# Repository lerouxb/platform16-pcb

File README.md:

# platform 16 PCB

This is the KiCad project for **platform 16** — a compact digital synthesizer built around the Raspberry Pi RP2350 microcontroller. The board hosts 16 potentiometers for real-time parameter control, a high-quality audio output chain, and USB-C for power and an SWD port for development.

## Overview

Platform 16 is a self-contained generative synthesizer platform. The hardware is designed to pair with swappable firmware engines — each one turns the same 16 knobs into a different instrument. A companion [front panel editor](https://github.com/lerouxb/platform16-editor) (web app) generates printable overlays so you can label the knobs for whichever [firmware](https://github.com/lerouxb/plaform16-firmware) is loaded.

## Key Components

| Component | Part | Role |
|---|---|---|
| MCU | **RP2350** (QFN-60) | Dual-core Cortex-M33 — runs synthesis DSP, reads pots, drives I2S audio |
| DAC | **PCM5100A** (TI) | 32-bit stereo I2S DAC — converts digital audio to line-level analog |
| Headphone amp | **PAM8908JER** | Capless stereo headphone amplifier — drives headphones without coupling caps |
| Flash | **W25Q128JVS** (Winbond) | 16 MB QSPI flash for firmware and data storage |
| Analog mux | **CD74HC4067SM** | 16-channel analog multiplexer — reads all 16 pots through a single ADC channel |
| Voltage regulator | **NCP1117-3.3** | 3.3 V LDO powered from USB 5 V |
| Audio jacks | **PJ-320D-A** (×3) | 3.5 mm TRS jacks edge-mounted through board notches |
| Connector | **USB-C 16-pin** | Power and data (with proper CC resistors for USB-C detection) |

## Board Details

- **Dimensions:** ~112 mm × 86 mm with rounded corners
- **Mounting:** 4 × M3 mounting holes in a 69 mm × 46 mm rectangle
- **Audio jacks:** Semicircular edge cutouts allow the 3.5 mm jack barrels to protrude through the top edge
- **Passives:** 0402 throughout for a compact layout
- **Potentiometers:** 16 × 10 kΩ through-hole pots (the namesake of the project)
- **Buttons:** 2 × tactile switches for boot mode and reset

## Architecture

```
USB-C (5V)
  │
  ├─► NCP1117 → 3.3V rail
  │
  ▼
RP2350 ──I2S──► PCM5100A (DAC) ──► PAM8908 (amp) ──► 3.5mm jacks
  │
  ├─► CD74HC4067 mux ◄── 16 pots
  ├─► QSPI flash (W25Q128)
  ├─► 2 buttons
  └─► Clock in/out
```

## Schematic

## PCB Layout

## 3D Render

## Related Projects

- **[Firmware](https://github.com/lerouxb/plaform16-firmware)** — C++ (Pico SDK) running on the RP2350. Three swappable generative synth engines:
  - **SDS** — Stochastic Decay Subtractive (PolyBLEP saw + Moog ladder filter, random sequencer)
  - **PMD** — Phase Modulation with Decay (2-operator FM triads, dual LFOs)
  - **TEP** — Two-tone Euclidean Polymeters (dual detunable saws, 3 independent Euclidean rhythms)
- **[Front Panel Editor](https://github.com/lerouxb/platform16-editor)** — React/TypeScript web app for designing printable panel overlays with labelled knobs matching each firmware's control layout

## Tools

- **KiCad 9.0** — schematic and PCB design
- **Fabrication Toolkit** — JLC-compatible production output (BOM, positions, netlist in `production/`)

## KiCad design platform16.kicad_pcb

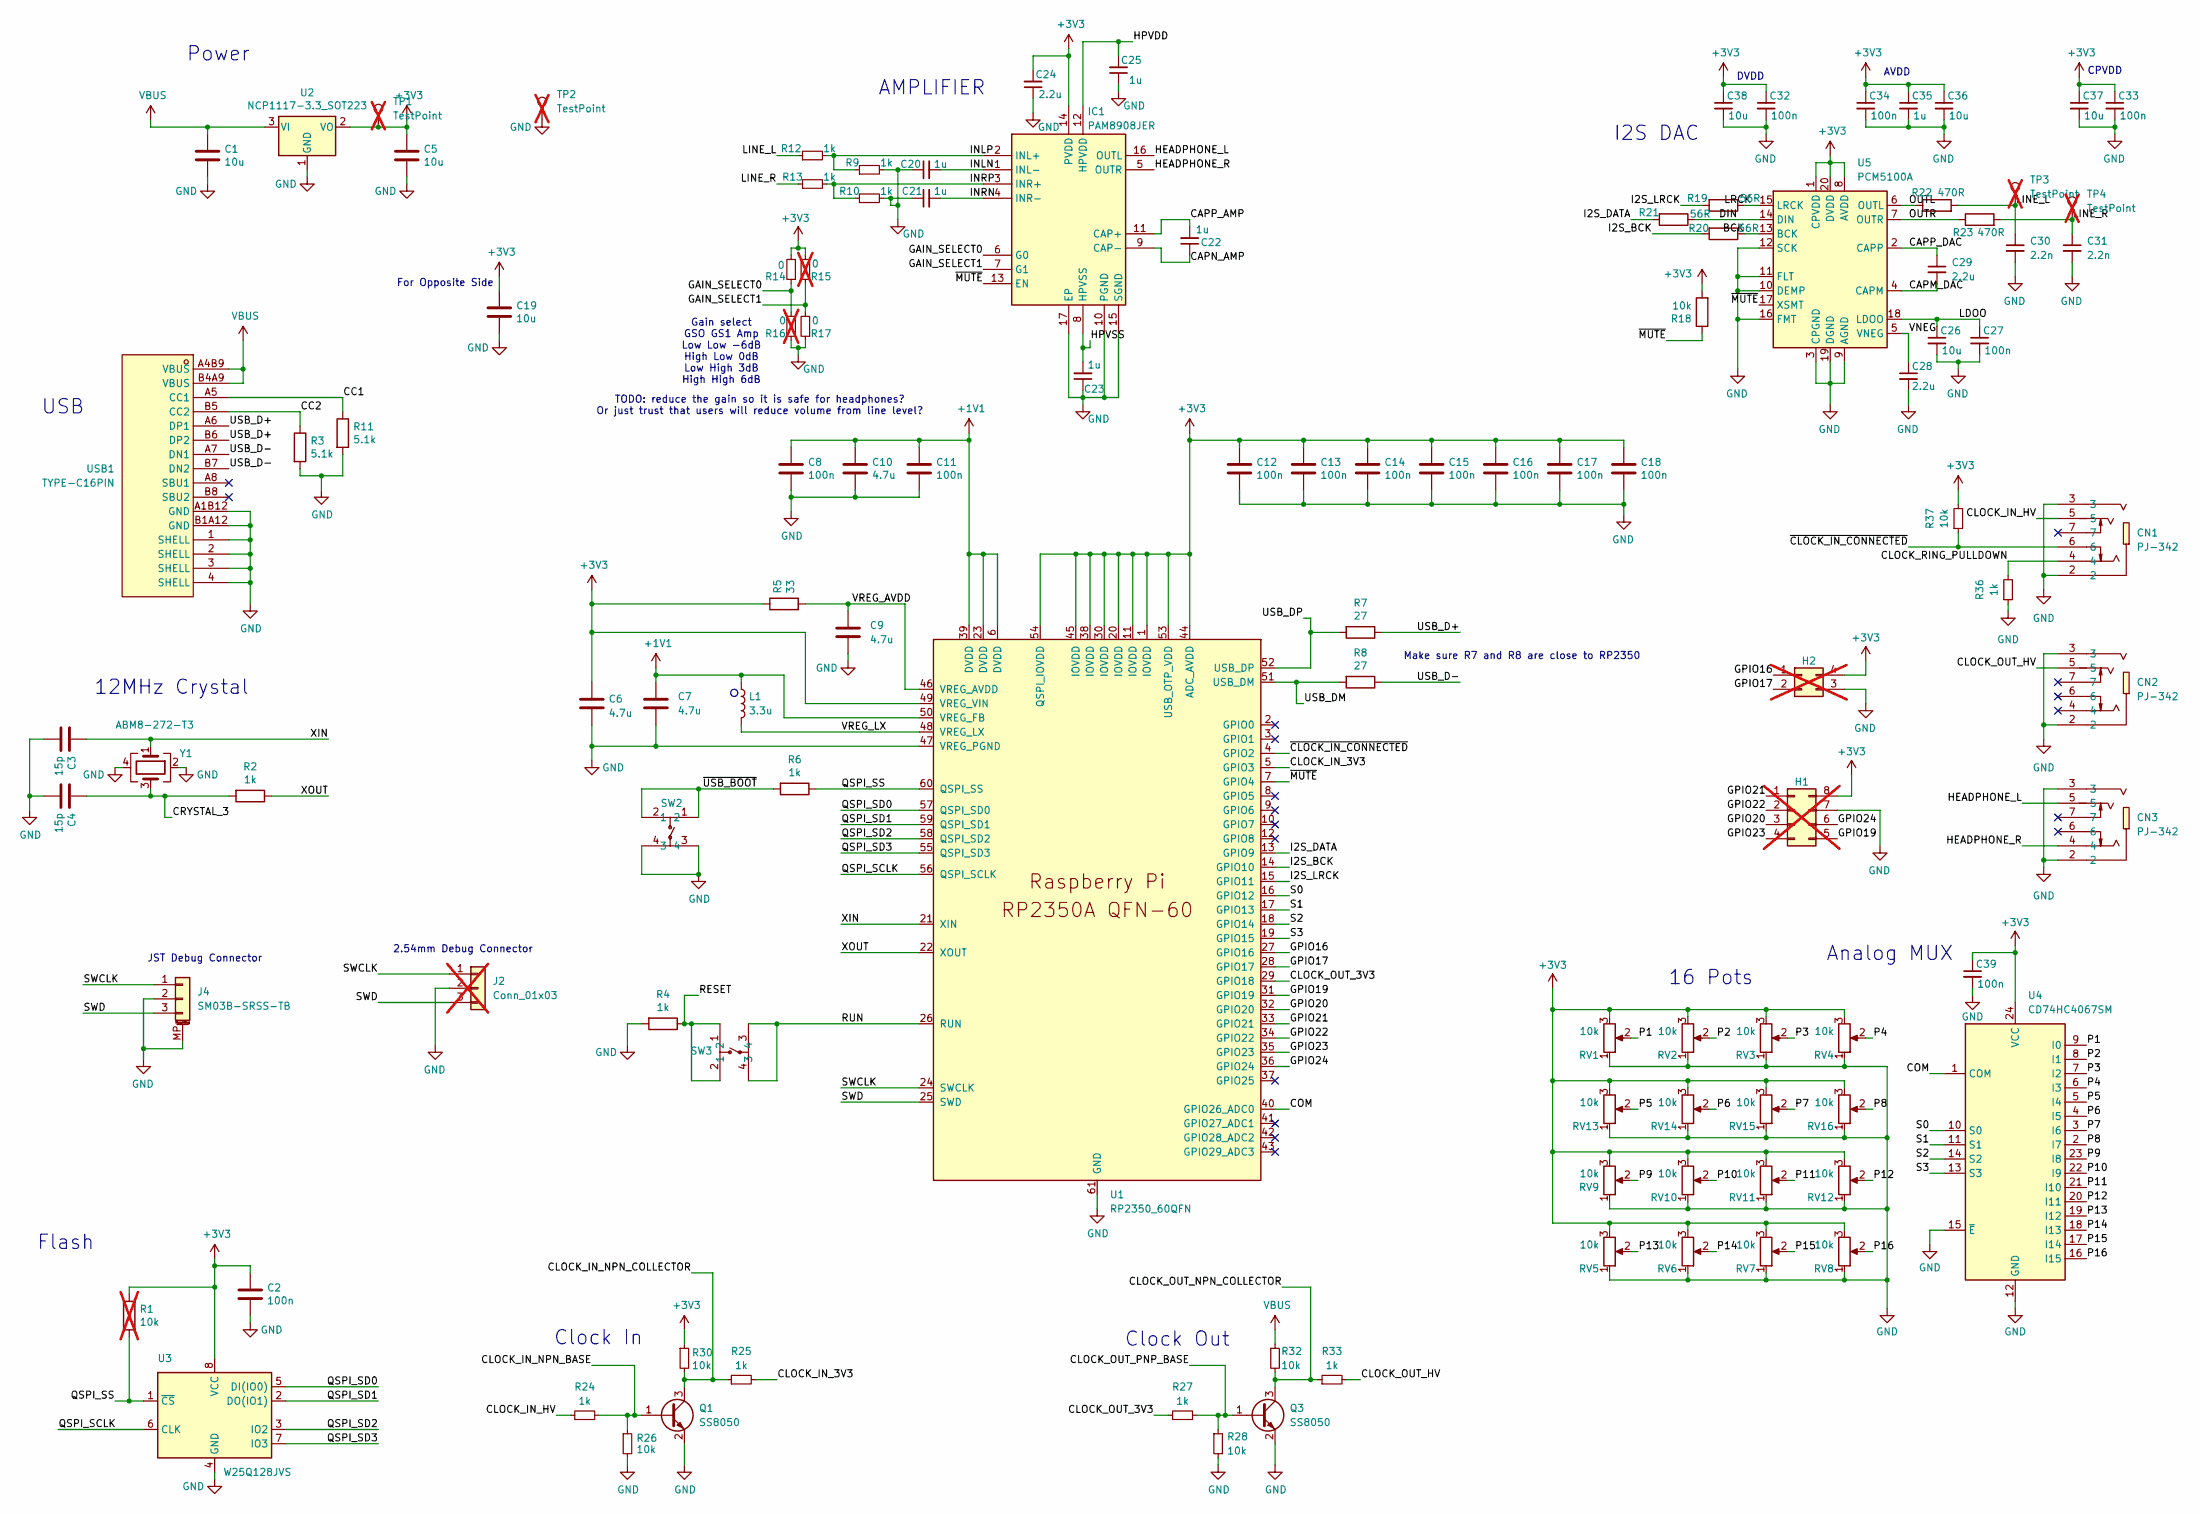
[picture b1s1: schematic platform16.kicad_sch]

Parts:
C1, C5, C19, C26, C36, C37, C38: 10u; C_0402_1005Metric_small_pads; LCSC C15525
C2, C8, C11, C12, C13, C14, C15, C16, C17, C18, C27, C32, C33, C34, C39: 100n; C_0402_1005Metric_small_pads; LCSC C1525
C3, C4: 15p; C_0402_1005Metric_small_pads; LCSC C1548
C6, C7, C9, C10: 4.7u; C_0402_1005Metric_small_pads; LCSC C23733
C20, C21, C22, C23, C25, C35: 1u; C_0402_1005Metric_small_pads; LCSC C52923
C24, C28, C29: 2.2u; C_0402_1005Metric_small_pads; LCSC C12530
C30, C31: 2.2n; C_0402_1005Metric_small_pads; LCSC C915853
CN1, CN2, CN3: PJ-342; AUDIO-SMD_PJ-342; LCSC C668606
H1: Conn_02x04_Counter_Clockwise; PinHeader_2x04_P1.27mm_Vertical; not fitted
H2: Conn_02x02_Counter_Clockwise; PinHeader_2x02_P1.27mm_Vertical; not fitted
IC1: PAM8908JER; QFN50P300X300X65-17N; Manufacturer_Part_Number PAM8908JER; Mouser Part Number 621-PAM8908JER
J2: Conn_01x03; PinHeader_1x03_P2.54mm_Vertical; not fitted
J4: SM03B-SRSS-TB; JST_SH_SM03B-SRSS-TB_1x03-1MP_P1.00mm_Horizontal; LCSC C160403
L1: 3.3u; L_pol_2016; LCSC C42411119
Q1, Q3: SS8050; SOT-23; LCSC C2150
R1: 10k; R_0402_1005Metric; LCSC C25744; not fitted
R2, R4, R6, R9, R10, R12, R13, R24, R25, R27, R33, R36: 1k; R_0402_1005Metric; LCSC C11702
R3, R11: 5.1k; R_0402_1005Metric; LCSC C25905
R5: 33; R_0402_1005Metric; LCSC C25105
R7, R8: 27; R_0402_1005Metric; LCSC C138021
R14, R17: 0; R_0402_1005Metric; LCSC C17168
R15, R16: 0; R_0402_1005Metric; LCSC C17168; not fitted
R18, R26, R28, R30, R32, R37: 10k; R_0402_1005Metric; LCSC C25744
R19, R20, R21: 56R; R_0402_1005Metric; LCSC C137957
R22, R23: 470R; R_0402_1005Metric; LCSC C25117
RV1, RV2, RV3, RV4, RV5, RV6, RV7, RV8, RV9, RV10, RV11, RV12, RV13, RV14, RV15, RV16: 10k; potentiometer; LCSC C470305
SW2, SW3: TS-1095PS-A165B2-C3D2; SW-SMD_4P-L6.0-W6.0-P4.50-LS9.2; LCSC C782843
TP1, TP2, TP3, TP4: TestPoint; TestPoint_THTPad_D4.0mm_Drill2.0mm; not fitted
U1: RP2350_60QFN; RP2350-QFN-60-1EP_7x7_P0.4mm_EP3.4x3.4mm_ThermalVias; LCSC C42411118
U2: NCP1117-3.3_SOT223; SOT-223-3_TabPin2; LCSC C26537
U3: W25Q128JVS; SOIC_208MIL_WIN; LCSC C97521
U4: CD74HC4067SM; SSOP-24_5.3x8.2mm_P0.65mm; LCSC C98457
U5: PCM5100A; TSSOP-20_4.4x6.5mm_P0.65mm; LCSC C131154
USB1: TYPE-C16PIN; USB-C-SMD_TYPE-C16PIN; LCSC Part C393939
Y1: ABM8-272-T3; Crystal_SMD_3225-4Pin_3.2x2.5mm; LCSC C20625731

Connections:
+1V1: C7.1, C8.1, C10.1, C11.1, L1.1, U1.6 (DVDD), U1.23 (DVDD), U1.39 (DVDD), U1.50 (VREG_FB)
+3V3: C2.1, C5.1, C6.1, C12.1, C13.1, C14.1, C15.1, C16.1, C17.1, C18.1, C19.1, C24.2, C32.1, C33.1, C34.1, C35.1, C36.1, C37.1, C38.1, C39.1, H1.8, H2.4, IC1.14 (PVDD), R1.1, R5.1, R14.2, R15.2, R18.2, R30.1, R37.2, RV1.3, RV2.3, RV3.3, RV4.3, RV5.3, RV6.3, RV7.3, RV8.3, RV9.3, RV10.3, RV11.3, RV12.3, RV13.3, RV14.3, RV15.3, RV16.3, TP1.1, U1.1 (IOVDD), U1.11 (IOVDD), U1.20 (IOVDD), U1.30 (IOVDD), U1.38 (IOVDD), U1.44 (ADC_AVDD), U1.45 (IOVDD), U1.49 (VREG_VIN), U1.53 (USB_OTP_VDD), U1.54 (QSPI_IOVDD), U2.2 (VO), U3.8 (VCC), U4.24 (VCC), U5.1 (CPVDD), U5.8 (AVDD), U5.20 (DVDD)
/BCK: R20.1, U5.13 (BCK)
/CAPM_DAC: C29.2, U5.4 (CAPM)
/CAPN_AMP: C22.1, IC1.9 (CAP-)
/CAPP_AMP: C22.2, IC1.11 (CAP+)
/CAPP_DAC: C29.1, U5.2 (CAPP)
/CC1: R11.1, USB1.A5 (CC1)
/CC2: R3.1, USB1.B5 (CC2)
/CLOCK_IN_3V3: R25.2, U1.5 (GPIO3)
/CLOCK_IN_HV: CN1.5, R24.1
/CLOCK_IN_NPN_BASE: Q1.1 (B), R24.2, R26.1
/CLOCK_IN_NPN_COLLECTOR: Q1.3 (C), R25.1, R30.2
/CLOCK_OUT_3V3: R27.1, U1.29 (GPIO18)
/CLOCK_OUT_HV: CN2.5, R33.2
/CLOCK_OUT_NPN_COLLECTOR: Q3.3 (C), R32.2, R33.1
/CLOCK_OUT_PNP_BASE: Q3.1 (B), R27.2, R28.1
/CLOCK_RING_PULLDOWN: CN1.4, R36.2
/COM: U1.40 (GPIO26_ADC0), U4.1 (COM)
/CRYSTAL_3: C4.1, R2.2, Y1.3
/DIN: R21.1, U5.14 (DIN)
/GAIN_SELECT0: IC1.6 (G0), R14.1, R16.2
/GAIN_SELECT1: IC1.7 (G1), R15.1, R17.2
/GPIO16: H2.1, U1.27 (GPIO16)
/GPIO17: H2.2, U1.28 (GPIO17)
/GPIO19: H1.5, U1.31 (GPIO19)
/GPIO20: H1.3, U1.32 (GPIO20)
/GPIO21: H1.1, U1.33 (GPIO21)
/GPIO22: H1.2, U1.34 (GPIO22)
/GPIO23: H1.4, U1.35 (GPIO23)
/GPIO24: H1.6, U1.36 (GPIO24)
/HEADPHONE_L: CN3.5, IC1.16 (OUTL)
/HEADPHONE_R: CN3.4, IC1.5 (OUTR)
/HPVDD: C25.2, IC1.12 (HPVDD)
/HPVSS: C23.2, IC1.8 (HPVSS)
/I2S_BCK: R20.2, U1.14 (GPIO10)
/I2S_DATA: R21.2, U1.13 (GPIO9)
/I2S_LRCK: R19.2, U1.15 (GPIO11)
/INLN: C20.2, IC1.1 (INL-)
/INLP: IC1.2 (INL+), R9.1, R12.2
/INRN: C21.2, IC1.4 (INR-)
/INRP: IC1.3 (INR+), R10.1, R13.2
/LDOO: C26.1, C27.1, U5.18 (LDOO)
/LINE_L: C30.1, R12.1, R22.2, TP3.1
/LINE_R: C31.1, R13.1, R23.2, TP4.1
/LRCK: R19.1, U5.15 (LRCK)
/OUTL: R22.1, U5.6 (OUTL)
/OUTR: R23.1, U5.7 (OUTR)
/P1: RV1.2, U4.9 (I0)
/P2: RV2.2, U4.8 (I1)
/P3: RV3.2, U4.7 (I2)
/P4: RV4.2, U4.6 (I3)
/P5: RV13.2, U4.5 (I4)
/P6: RV14.2, U4.4 (I5)
/P7: RV15.2, U4.3 (I6)
/P8: RV16.2, U4.2 (I7)
/P9: RV9.2, U4.23 (I8)
/P10: RV10.2, U4.22 (I9)
/P11: RV11.2, U4.21 (I10)
/P12: RV12.2, U4.20 (I11)
/P13: RV5.2, U4.19 (I12)
/P14: RV6.2, U4.18 (I13)
/P15: RV7.2, U4.17 (I14)
/P16: RV8.2, U4.16 (I15)
/QSPI_SCLK: U1.56 (QSPI_SCLK), U3.6 (CLK)
/QSPI_SD0: U1.57 (QSPI_SD0), U3.5 (DI(IO0))
/QSPI_SD1: U1.59 (QSPI_SD1), U3.2 (DO(IO1))
/QSPI_SD2: U1.58 (QSPI_SD2), U3.3 (IO2)
/QSPI_SD3: U1.55 (QSPI_SD3), U3.7 (IO3)
/QSPI_SS: R1.2, R6.1, U1.60 (QSPI_SS), U3.1 (~CS)
/RESET: R4.1, SW3.1, SW3.2
/RUN: SW3.3, SW3.4, U1.26 (RUN)
/S0: U1.16 (GPIO12), U4.10 (S0)
/S1: U1.17 (GPIO13), U4.11 (S1)
/S2: U1.18 (GPIO14), U4.14 (S2)
/S3: U1.19 (GPIO15), U4.13 (S3)
/SWCLK: J2.1, J4.1, U1.24 (SWCLK)
/SWD: J2.3, J4.3, U1.25 (SWD)
/USB_D+: R7.1, USB1.A6 (DP1), USB1.B6 (DP2)
/USB_D-: R8.1, USB1.A7 (DN1), USB1.B7 (DN2)
/USB_DM: R8.2, U1.51 (USB_DM)
/USB_DP: R7.2, U1.52 (USB_DP)
/VNEG: C28.1, U5.5 (VNEG)
/VREG_AVDD: C9.1, R5.2, U1.46 (VREG_AVDD)
/VREG_LX: L1.2, U1.48 (VREG_LX)
/XIN: C3.1, U1.21 (XIN), Y1.1
/XOUT: R2.1, U1.22 (XOUT)
/~CLOCK_IN_CONNECTED: CN1.6, R37.1, U1.4 (GPIO2)
/~MUTE: IC1.13 (EN), R18.1, U1.7 (GPIO4), U5.17 (XSMT)
/~USB_BOOT: R6.2, SW2.1, SW2.2
GND: C1.2, C2.2, C3.2, C4.2, C5.2, C6.2, C7.2, C8.2, C9.2, C10.2, C11.2, C12.2, C13.2, C14.2, C15.2, C16.2, C17.2, C18.2, C19.2, C20.1, C21.1, C23.1, C24.1, C25.1, C26.2, C27.2, C28.2, C30.2, C31.2, C32.2, C33.2, C34.2, C35.2, C36.2, C37.2, C38.2, C39.2, CN1.2, CN1.3, CN2.2, CN2.3, CN3.2, CN3.3, H1.7, H2.3, IC1.10 (PGND), IC1.15 (SGND), IC1.17 (EP), J2.2, J4.2, J4.MP (MountPin), Q1.2 (E), Q3.2 (E), R3.2, R4.2, R9.2, R10.2, R11.2, R16.1, R17.1, R26.2, R28.2, R36.1, RV1.1, RV2.1, RV3.1, RV4.1, RV5.1, RV6.1, RV7.1, RV8.1, RV9.1, RV10.1, RV11.1, RV12.1, RV13.1, RV14.1, RV15.1, RV16.1, SW2.3, SW2.4, TP2.1, U1.47 (VREG_PGND), U1.61 (GND), U2.1 (GND), U3.4 (GND), U4.12 (GND), U4.15 (~E), U5.3 (CPGND), U5.9 (AGND), U5.10 (DEMP), U5.11 (FLT), U5.12 (SCK), U5.16 (FMT), U5.19 (DGND), USB1.1 (SHELL), USB1.2 (SHELL), USB1.3 (SHELL), USB1.4 (SHELL), USB1.A1B12 (GND), USB1.B1A12 (GND), Y1.2, Y1.4
VBUS: C1.1, R32.1, U2.3 (VI), USB1.A4B9 (VBUS), USB1.B4A9 (VBUS)

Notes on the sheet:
CPVDD
JST Debug Connector
For Opposite Side
16 Pots
USB
Clock In
AMPLIFIER
AVDD
TODO: reduce the gain so it is safe for headphones? Or just trust that users will reduce volume from line level?
Flash
Clock Out
I2S DAC
2.54mm Debug Connector
Make sure R7 and R8 are close to RP2350
Analog MUX
Gain select GSO GS1 Amp Low Low -6dB High Low 0dB Low High 3dB High High 6dB
DVDD
12MHz Crystal
Power

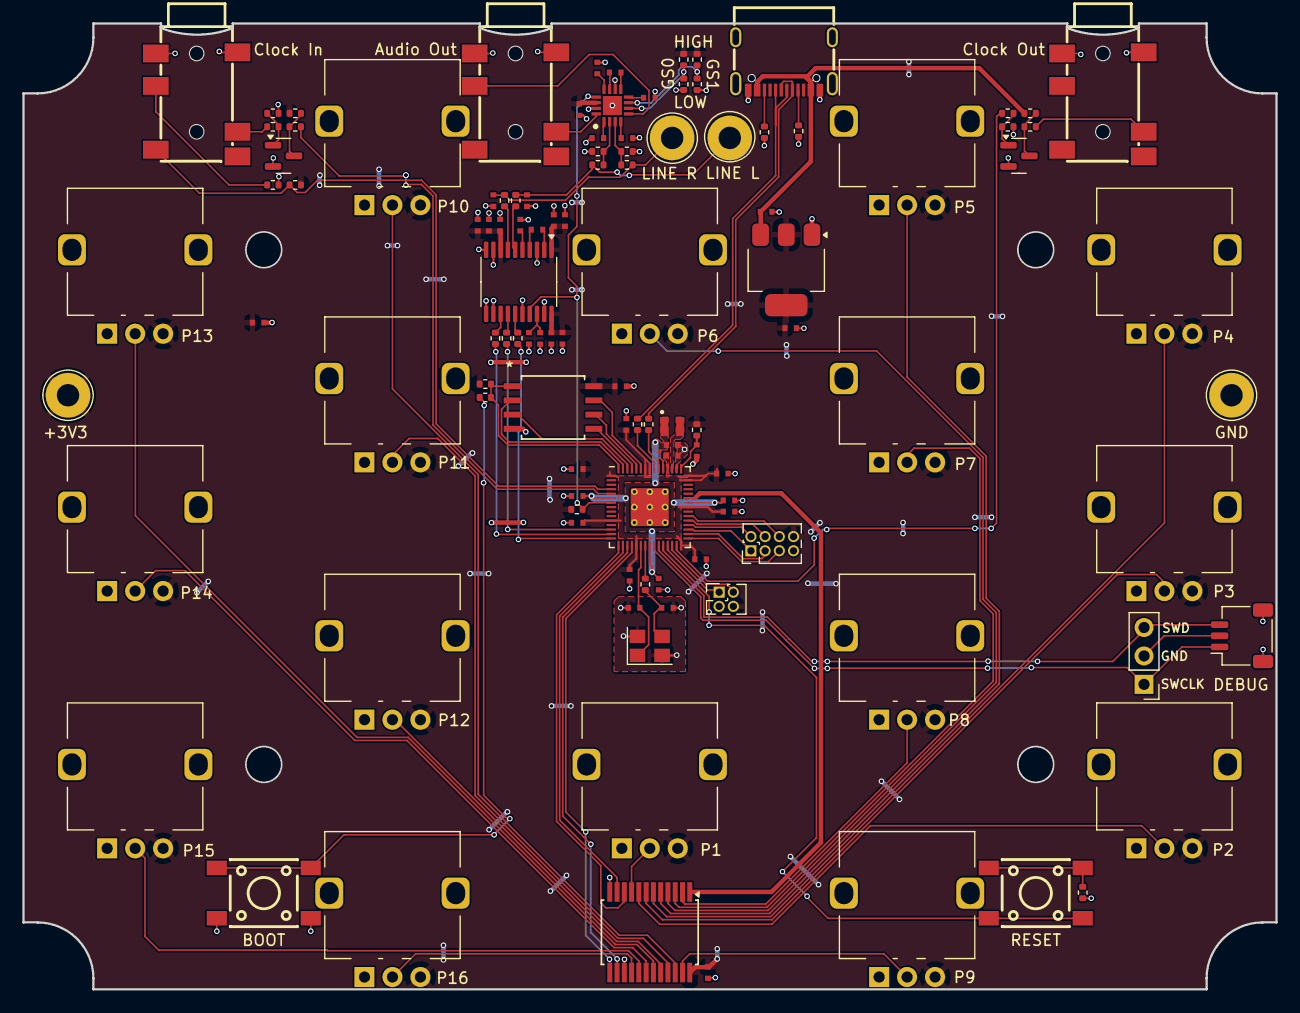
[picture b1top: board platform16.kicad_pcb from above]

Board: 2 copper layers, 112.0 x 86.3 mm, 112 parts (0 on the bottom side), 92 nets.

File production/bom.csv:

Designator,Footprint,Quantity,Value,LCSC Part #
"C1, C19, C26, C36, C37, C38, C5",0402,7,10u,C15525
"C10, C6, C7, C9",0402,4,4.7u,C23733
"C11, C12, C13, C14, C15, C16, C17, C18, C2, C27, C32, C33, C34, C39, C8",0402,15,100n,C1525
"C20, C21, C22, C23, C25, C35",0402,6,1u,C52923
"C24, C28, C29",0402,3,2.2u,C12530
"C3, C4",0402,2,15p,C1548
"C30, C31",0402,2,2.2n,C915853
"CN1, CN2, CN3",AUDIO-SMD_PJ-342,3,PJ-342,C668606
IC1,QFN50P300X300X65-17N,1,PAM8908JER,C33233
J4,JST_SH_SM03B-SRSS-TB_1x03-1MP_P1.00mm_Horizontal,1,SM03B-SRSS-TB,C160403
L1,L_pol_2016,1,3.3u,C42411119
"Q1, Q3",SOT-23,2,SS8050,C2150
"R10, R12, R13, R2, R24, R25, R27, R33, R36, R4, R6, R9",0402,12,1k,C11702
"R11, R3",0402,2,5.1k,C25905
"R14, R17",0402,2,0,C17168
"R18, R26, R28, R30, R32, R37",0402,6,10k,C25744
"R19, R20, R21",0402,3,56R,C137957
"R22, R23",0402,2,470R,C25117
R5,0402,1,33,C25105
"R7, R8",0402,2,27,C138021
"RV1, RV10, RV11, RV12, RV13, RV14, RV15, RV16, RV2, RV3, RV4, RV5, RV6, RV7, RV8, RV9",potentiometer,16,10k,C470305
"SW2, SW3",SW-SMD_4P-L6.0-W6.0-P4.50-LS9.2,2,TS-1095PS-A165B2-C3D2,C782843
U1,RP2350-QFN-60-1EP_7x7_P0.4mm_EP3.4x3.4mm_ThermalVias,1,RP2350_60QFN,C42411118
U2,SOT-223-3_TabPin2,1,NCP1117-3.3_SOT223,C26537
U3,SOIC_208MIL_WIN,1,W25Q128JVS,C97521
U4,SSOP-24_5.3x8.2mm_P0.65mm,1,CD74HC4067SM,C98457
U5,TSSOP-20_4.4x6.5mm_P0.65mm,1,PCM5100A,C131154
USB1,USB-C-SMD_TYPE-C16PIN,1,TYPE-C16PIN,C393939
Y1,Crystal_SMD_3225-4Pin_3.2x2.5mm,1,ABM8-272-T3,C20625731

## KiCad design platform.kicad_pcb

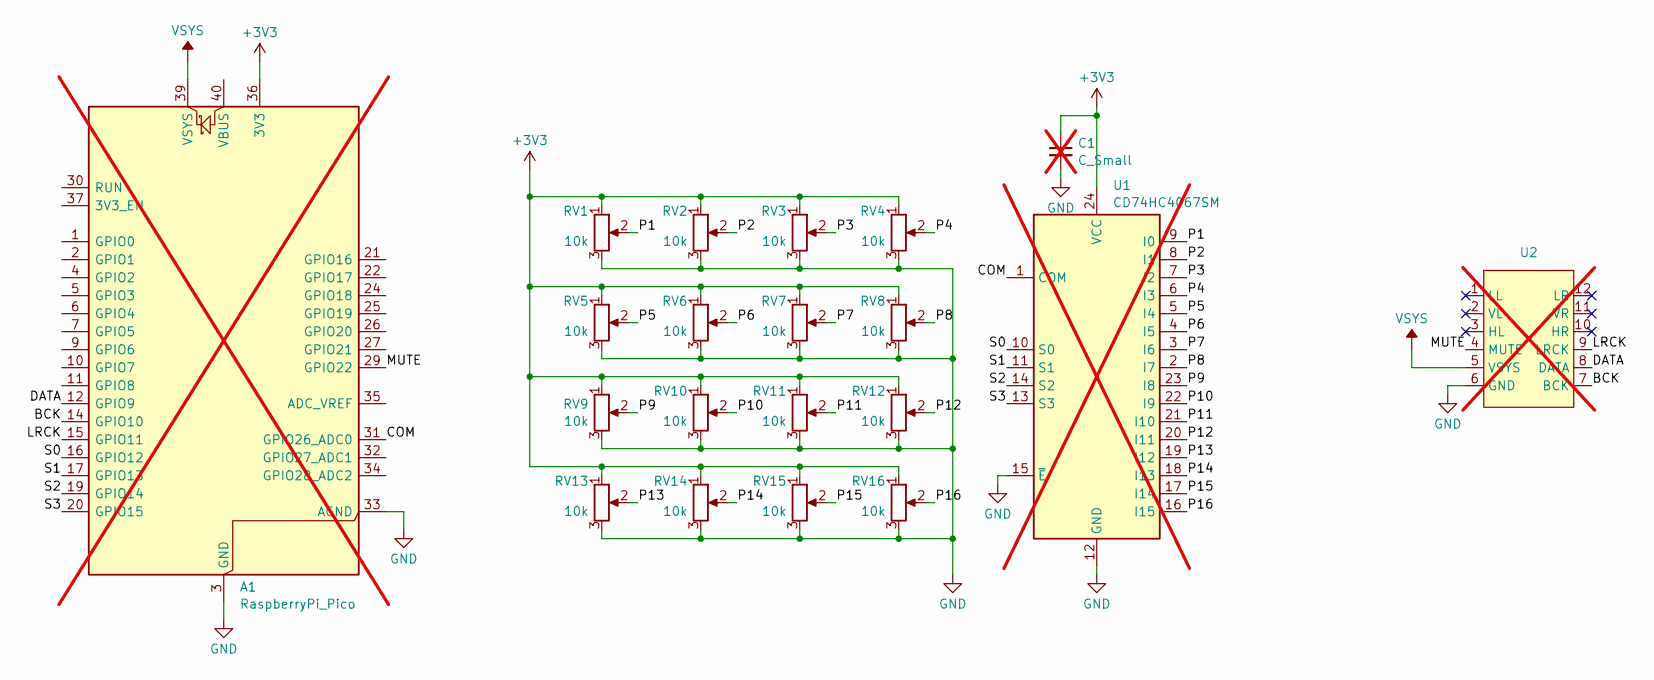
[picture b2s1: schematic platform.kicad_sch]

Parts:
A1: RaspberryPi_Pico; RaspberryPi_Pico_SMD; not fitted
C1: C_Small; C_0805_2012Metric; not fitted
RV1, RV2, RV3, RV4, RV5, RV6, RV7, RV8, RV9, RV10, RV11, RV12, RV13, RV14, RV15, RV16: 10k; potentiometer; LCSC C209779
U1: CD74HC4067SM; SSOP-24_5.3x8.2mm_P0.65mm; not fitted
U2: audio-out-module; not fitted

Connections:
+3V3: A1.36 (3V3), C1.1, RV1.1, RV2.1, RV3.1, RV4.1, RV5.1, RV6.1, RV7.1, RV8.1, RV9.1, RV10.1, RV11.1, RV12.1, RV13.1, RV14.1, RV15.1, RV16.1, U1.24 (VCC)
/BCK: A1.14 (GPIO10), U2.7 (BCK)
/COM: A1.31 (GPIO26_ADC0), U1.1 (COM)
/DATA: A1.12 (GPIO9), U2.8 (DATA)
/LRCK: A1.15 (GPIO11), U2.9 (LRCK)
/MUTE: A1.29 (GPIO22), U2.4 (MUTE)
/P1: RV1.2, U1.9 (I0)
/P2: RV2.2, U1.8 (I1)
/P3: RV3.2, U1.7 (I2)
/P4: RV4.2, U1.6 (I3)
/P5: RV5.2, U1.5 (I4)
/P6: RV6.2, U1.4 (I5)
/P7: RV7.2, U1.3 (I6)
/P8: RV8.2, U1.2 (I7)
/P9: RV9.2, U1.23 (I8)
/P10: RV10.2, U1.22 (I9)
/P11: RV11.2, U1.21 (I10)
/P12: RV12.2, U1.20 (I11)
/P13: RV13.2, U1.19 (I12)
/P14: RV14.2, U1.18 (I13)
/P15: RV15.2, U1.17 (I14)
/P16: RV16.2, U1.16 (I15)
/S0: A1.16 (GPIO12), U1.10 (S0)
/S1: A1.17 (GPIO13), U1.11 (S1)
/S2: A1.19 (GPIO14), U1.14 (S2)
/S3: A1.20 (GPIO15), U1.13 (S3)
GND: A1.3 (GND), A1.8 (GND), A1.13 (GND), A1.18 (GND), A1.23 (GND), A1.28 (GND), A1.33 (AGND), A1.38 (GND), C1.2, RV1.3, RV2.3, RV3.3, RV4.3, RV5.3, RV6.3, RV7.3, RV8.3, RV9.3, RV10.3, RV11.3, RV12.3, RV13.3, RV14.3, RV15.3, RV16.3, U1.12 (GND), U1.15 (~E), U2.6 (GND)
VSYS: A1.39 (VSYS), U2.5 (VSYS)

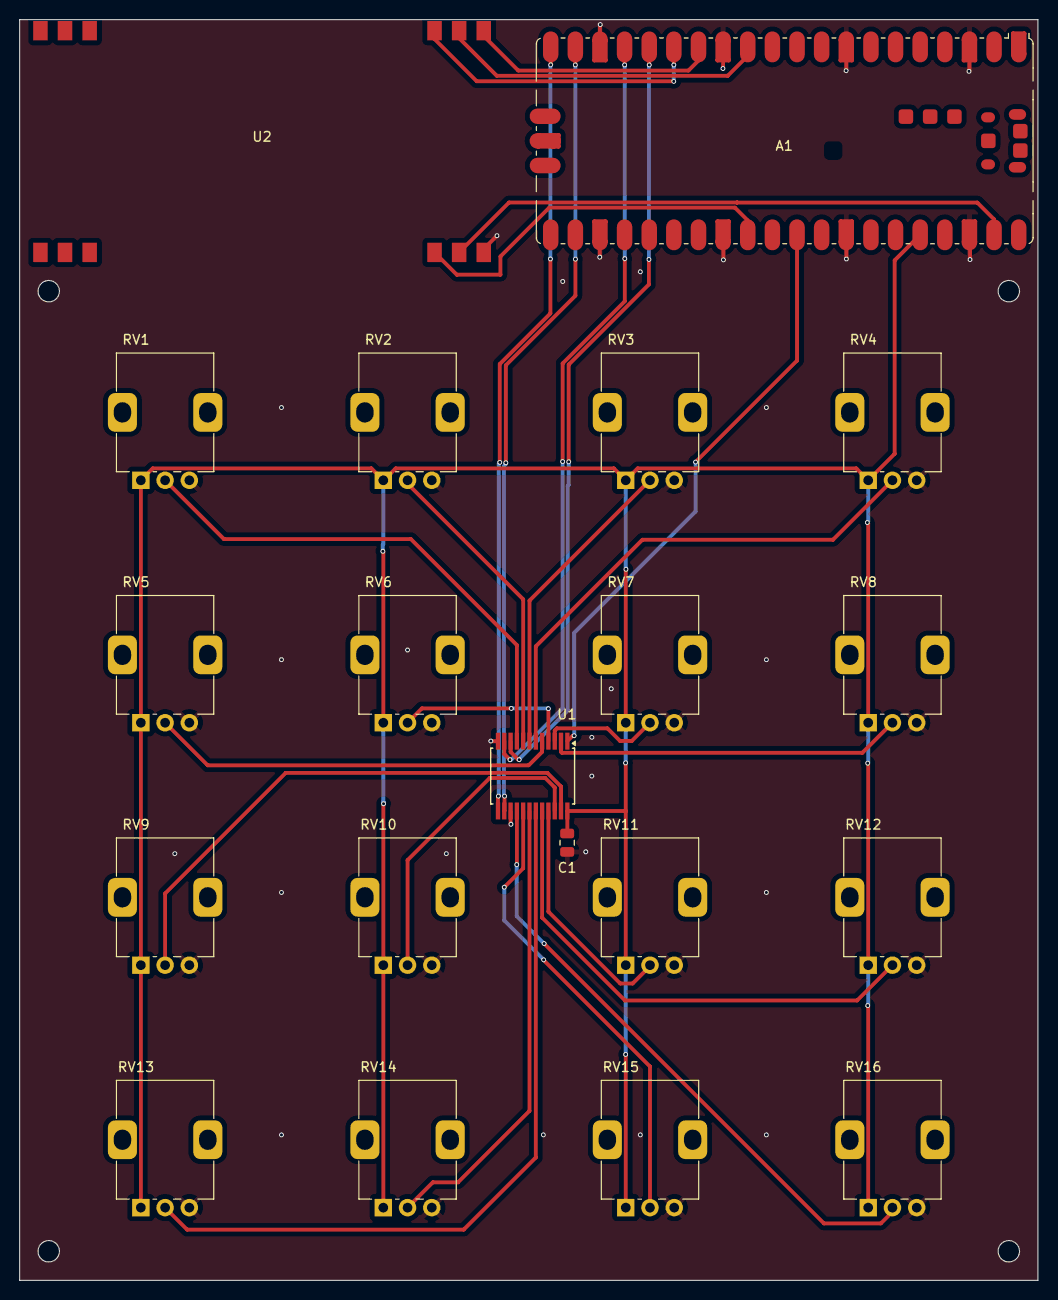
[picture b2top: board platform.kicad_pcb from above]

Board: 2 copper layers, 105.0 x 130.0 mm, 20 parts (0 on the bottom side), 28 nets.

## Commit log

2025-02-17 initial design
2025-04-23 16 pots, clock in, audio out, clock out, boot, reset
2025-04-25 move ports around a bit
2025-05-22 tweaks
2025-06-07 another iteration
2025-06-20 potentiometer tweaks
2026-03-28 basic readme
2026-03-28 finally a proper README
